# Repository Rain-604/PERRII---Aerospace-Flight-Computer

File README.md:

# PERRII – Aerospace Flight Computer

## Project Overview
PERRII is a modular aerospace flight computer designed for environmental sensing and long-range data telemetry. The system is built around the ESP32-S3 Zero microcontroller and is designed to function as a scientific payload for high-altitude ballooning or atmospheric research. It integrates precision GNSS positioning, environmental gas sensing (Methane and Ammonia), and a robust power regulation system.

## My Contribution: LoRa Communication Subsystem
As the lead for the communication system, I was responsible for the hardware integration and signal integrity of the long-range telemetry link.

### Key Technical Implementations:
* **RFM98W Integration**: Integrated the RFM98W-433S2 LoRa transceiver to provide a robust, low-power, long-distance communication link between the flight computer and the ground station.
* **RF Hardware Design**: Designed the antenna interface for the AE1 Antenna, including a 100pF decoupling capacitor (C5) to ensure signal stability.
* **SPI Interface Management**: Configured the SPI bus (MOSI, MISO, SCK, NSS) to interface the RF module with the ESP32-S3, managing critical interrupt lines (DIO0-DIO5) for real-time packet handling.
* **RF Layout Optimization**: Optimized the trace routing between the RF transceiver and the antenna connector to maintain signal integrity in a compact, circular PCB form factor.

## System Architecture
While my primary focus was the communication link, I worked closely with the team to integrate the following subsystems:

### 1. Navigation & Sensing
* **GNSS Positioning**: Integration of a u-blox CAM-M8C-D GPS module for real-time tracking.
* **Environmental Monitoring**: Active monitoring of atmospheric data via SEN1 (Methane) and SEN2 (Ammonia) gas sensors.
* **Visual Telemetry**: A dedicated LED altitude output array driven by the AW9523B LED driver.

### 2. Power Management
* **Dual-Stage Regulation**: The system utilizes a high-efficiency LM2596S-5 switching buck converter for the primary 5V rail and an LM1117DT-3.3 LDO for the sensitive logic and RF rails.
* **Robust Input**: Featuring XT-30 battery connectors and reverse polarity protection via a D10 Schottky diode.

## Design Files
### 1. Schematic Design
The schematic follows a modular design separated into Power, TX, Sensor, and GPS blocks.

### 2. PCB Layout
A circular 2-layer board designed for cylindrical aerospace housing.

## Team & Credits
* **Lok Yu Lui (Rain)**: Hardware Engineer – LoRa Communication Subsystem.
* **PERRII Team**: Collaborative effort for MCU integration, Power Systems, and Sensor Payloads.

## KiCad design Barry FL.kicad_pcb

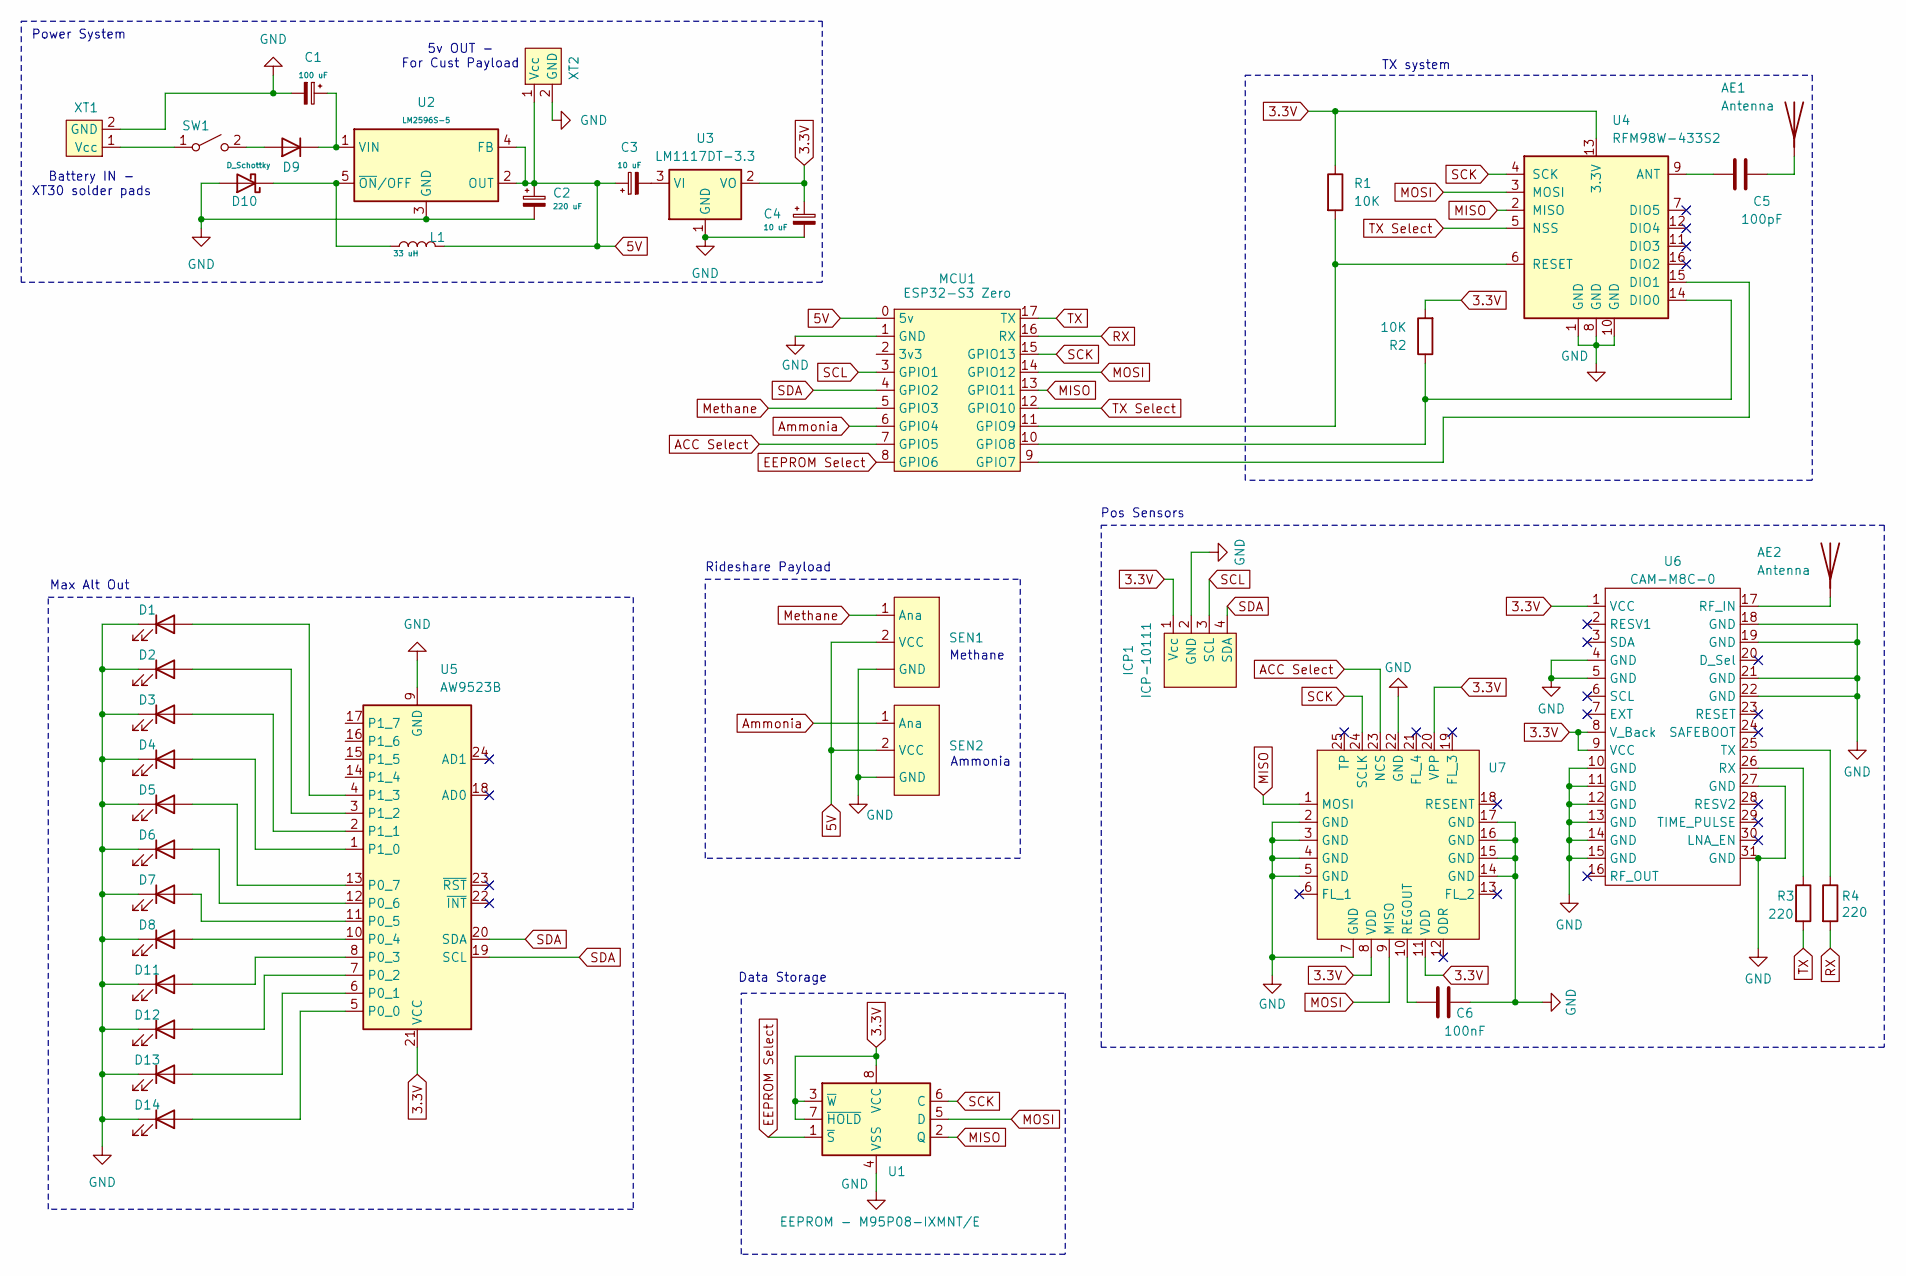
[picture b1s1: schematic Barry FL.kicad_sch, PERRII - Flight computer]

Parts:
AE1: Antenna; 132203
AE2: Antenna
C1: 100 uF
C2: 220 uF
C3, C4: 10 uF
C5: 100pF
C6: 100nF
D1, D2, D3, D4, D5, D6, D7, D8, D11, D12, D13, D14: LED; LED_0603_1608Metric_Pad1.05x0.95mm_HandSolder
D9: 1N4148WT; D_SOD-523
D10: D_Schottky
ICP1: ICP-10111
L1: 33 uH
MCU1: ESP32-S3 Zero; ESP32-S3 Zero Mini Development Board
R1, R2: 10K; R_0603_1608Metric_Pad0.98x0.95mm_HandSolder
R3, R4: 220; R_0603_1608Metric_Pad0.98x0.95mm_HandSolder
SEN1, SEN2: SEN Footprint
SW1: Jumper
U1: EEPROM - M95P08-IXMNT/E; SOIC-8_3.9x4.9mm_P1.27mm
U2: LM2596S-5; TO-263-5_TabPin3
U3: LM1117DT-3.3; TO-252-3_TabPin2
U4: RFM98W-433S2
U5: AW9523B; QFN-24-1EP_4x4mm_P0.5mm_EP2.7x2.7mm
U6: CAM-M8C-0
U7: (no value)
XT1, XT2: XT_30

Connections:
3.3V: C4.1, ICP1.1 (Vcc), R1.1, R2.2, U1.3 (~W), U1.7 (~HOLD), U1.8 (VCC), U3.2 (VO), U4.13 (3.3V), U5.21 (VCC), U6.1 (VCC), U6.8 (V_Back), U6.9 (VCC), U7.8 (VDD), U7.11 (VDD), U7.20 (VPP)
5V: C2.1, C3.1, L1.2, MCU1.0 (5v), SEN1.2 (VCC), SEN2.2 (VCC), U2.2 (OUT), U2.4 (FB), XT2.1 (Vcc)
ACC Select: MCU1.7 (GPIO5), U7.23 (NCS)
Ammonia: MCU1.6 (GPIO4), SEN2.1 (Ana)
EEPROM Select: MCU1.8 (GPIO6), U1.1 (~S)
GND: C1.2, C2.2, C4.2, C6.1, D1.1 (K), D2.1 (K), D3.1 (K), D4.1 (K), D5.1 (K), D6.1 (K), D7.1 (K), D8.1 (K), D10.2 (A), D11.1 (K), D12.1 (K), D13.1 (K), D14.1 (K), ICP1.2 (GND), MCU1.1 (GND), SEN1. (GND), SEN1.3 (GND), SEN2. (GND), SEN2.3 (GND), U1.4 (VSS), U2.3 (GND), U3.1 (GND), U4.1 (GND), U4.8 (GND), U4.10 (GND), U5.9 (GND), U5.25 (GND), U6.4 (GND), U6.5 (GND), U6.10 (GND), U6.11 (GND), U6.12 (GND), U6.13 (GND), U6.14 (GND), U6.15 (GND), U6.18 (GND), U6.19 (GND), U6.21 (GND), U6.22 (GND), U6.27 (GND), U6.31 (GND), U7.2 (GND), U7.3 (GND), U7.4 (GND), U7.5 (GND), U7.7 (GND), U7.14 (GND), U7.15 (GND), U7.16 (GND), U7.17 (GND), U7.22 (GND), XT1.2 (GND), XT2.2 (GND)
MISO: MCU1.13 (GPIO11), U1.2 (Q), U4.2 (MISO), U7.1 (MOSI)
MOSI: MCU1.14 (GPIO12), U1.5 (D), U4.3 (MOSI), U7.9 (MISO)
Methane: MCU1.5 (GPIO3), SEN1.1 (Ana)
unnamed: AE1.1 (A), C5.1
unnamed: AE2.1 (A), U6.17 (RF_IN)
unnamed: D1.2 (A), U5.4 (P1_3)
unnamed: D2.2 (A), U5.3 (P1_2)
unnamed: D3.2 (A), U5.2 (P1_1)
unnamed: D4.2 (A), U5.1 (P1_0)
unnamed: D5.2 (A), U5.13 (P0_7)
unnamed: D6.2 (A), U5.12 (P0_6)
unnamed: D7.2 (A), U5.11 (P0_5)
unnamed: D8.2 (A), U5.10 (P0_4)
unnamed: D9.2 (A), SW1.2 (B)
unnamed: C1.1, D9.1 (K), U2.1 (VIN)
unnamed: D10.1 (K), L1.1, U2.5 (~ON/OFF)
unnamed: D11.2 (A), U5.8 (P0_3)
unnamed: D12.2 (A), U5.7 (P0_2)
unnamed: D13.2 (A), U5.6 (P0_1)
unnamed: D14.2 (A), U5.5 (P0_0)
unnamed: MCU1.9 (GPIO7), U4.15 (DIO1)
unnamed: MCU1.10 (GPIO8), R2.1, U4.14 (DIO0)
unnamed: MCU1.11 (GPIO9), R1.2, U4.6 (RESET)
unnamed: SW1.1 (A), XT1.1 (Vcc)
unnamed: C3.2, U3.3 (VI)
unnamed: C5.2, U4.9 (ANT)
unnamed: R3.1, U6.26 (RX)
unnamed: R4.1, U6.25 (TX)
unnamed: C6.2, U7.10 (REGOUT)
RX: MCU1.16 (RX), R4.2
SCK: MCU1.15 (GPIO13), U1.6 (C), U4.4 (SCK), U7.24 (SCLK)
SCL: ICP1.3 (SCL), MCU1.3 (GPIO1)
SDA: ICP1.4 (SDA), MCU1.4 (GPIO2), U5.19 (SCL), U5.20 (SDA)
TX: MCU1.17 (TX), R3.2
TX Select: MCU1.12 (GPIO10), U4.5 (NSS)

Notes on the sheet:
Data Storage
Power System
Battery IN - XT30 solder pads
Pos Sensors
Ammonia
Max Alt Out
TX system
Methane
Rideshare Payload
5v OUT - For Cust Payload

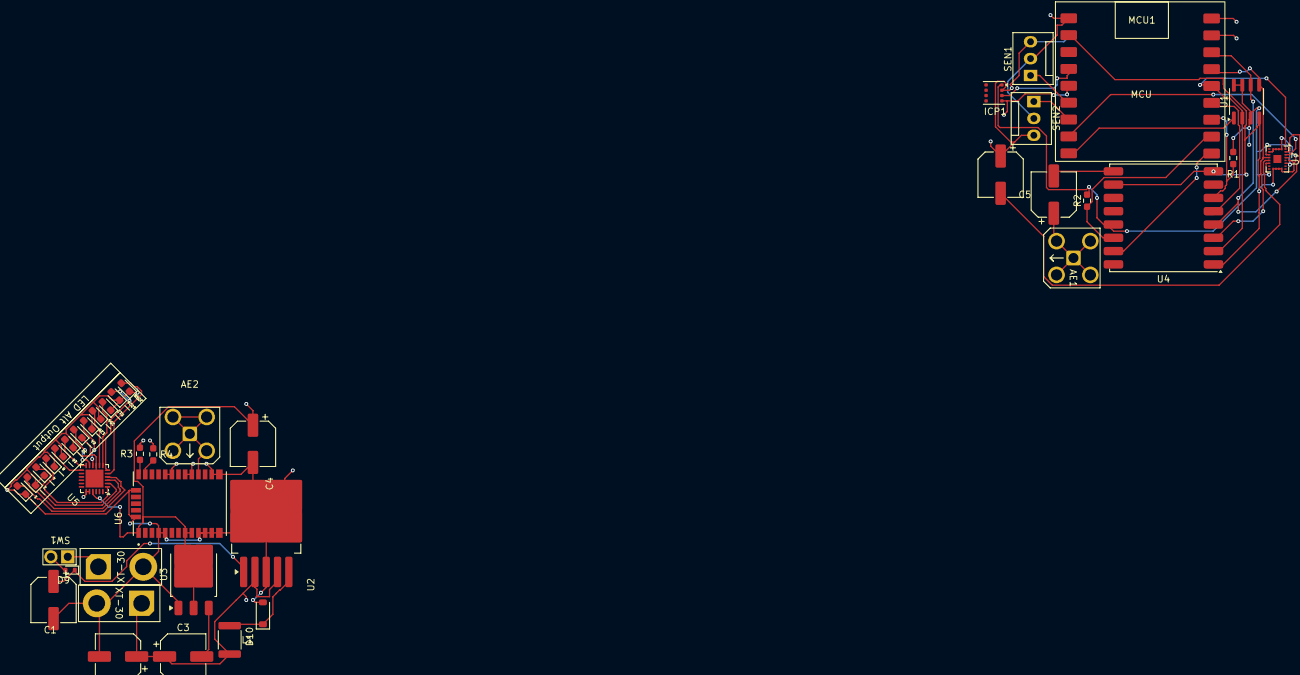
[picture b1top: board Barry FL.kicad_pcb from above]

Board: 2 copper layers, 41 parts (0 on the bottom side), 41 nets.

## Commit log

2026-05-04 Initialize README with project details and contributions
    Added detailed project overview, contributions, system architecture, and design files for the PERRII aerospace flight computer.
2026-05-04 Rename image_58648.png to image_586484.png
